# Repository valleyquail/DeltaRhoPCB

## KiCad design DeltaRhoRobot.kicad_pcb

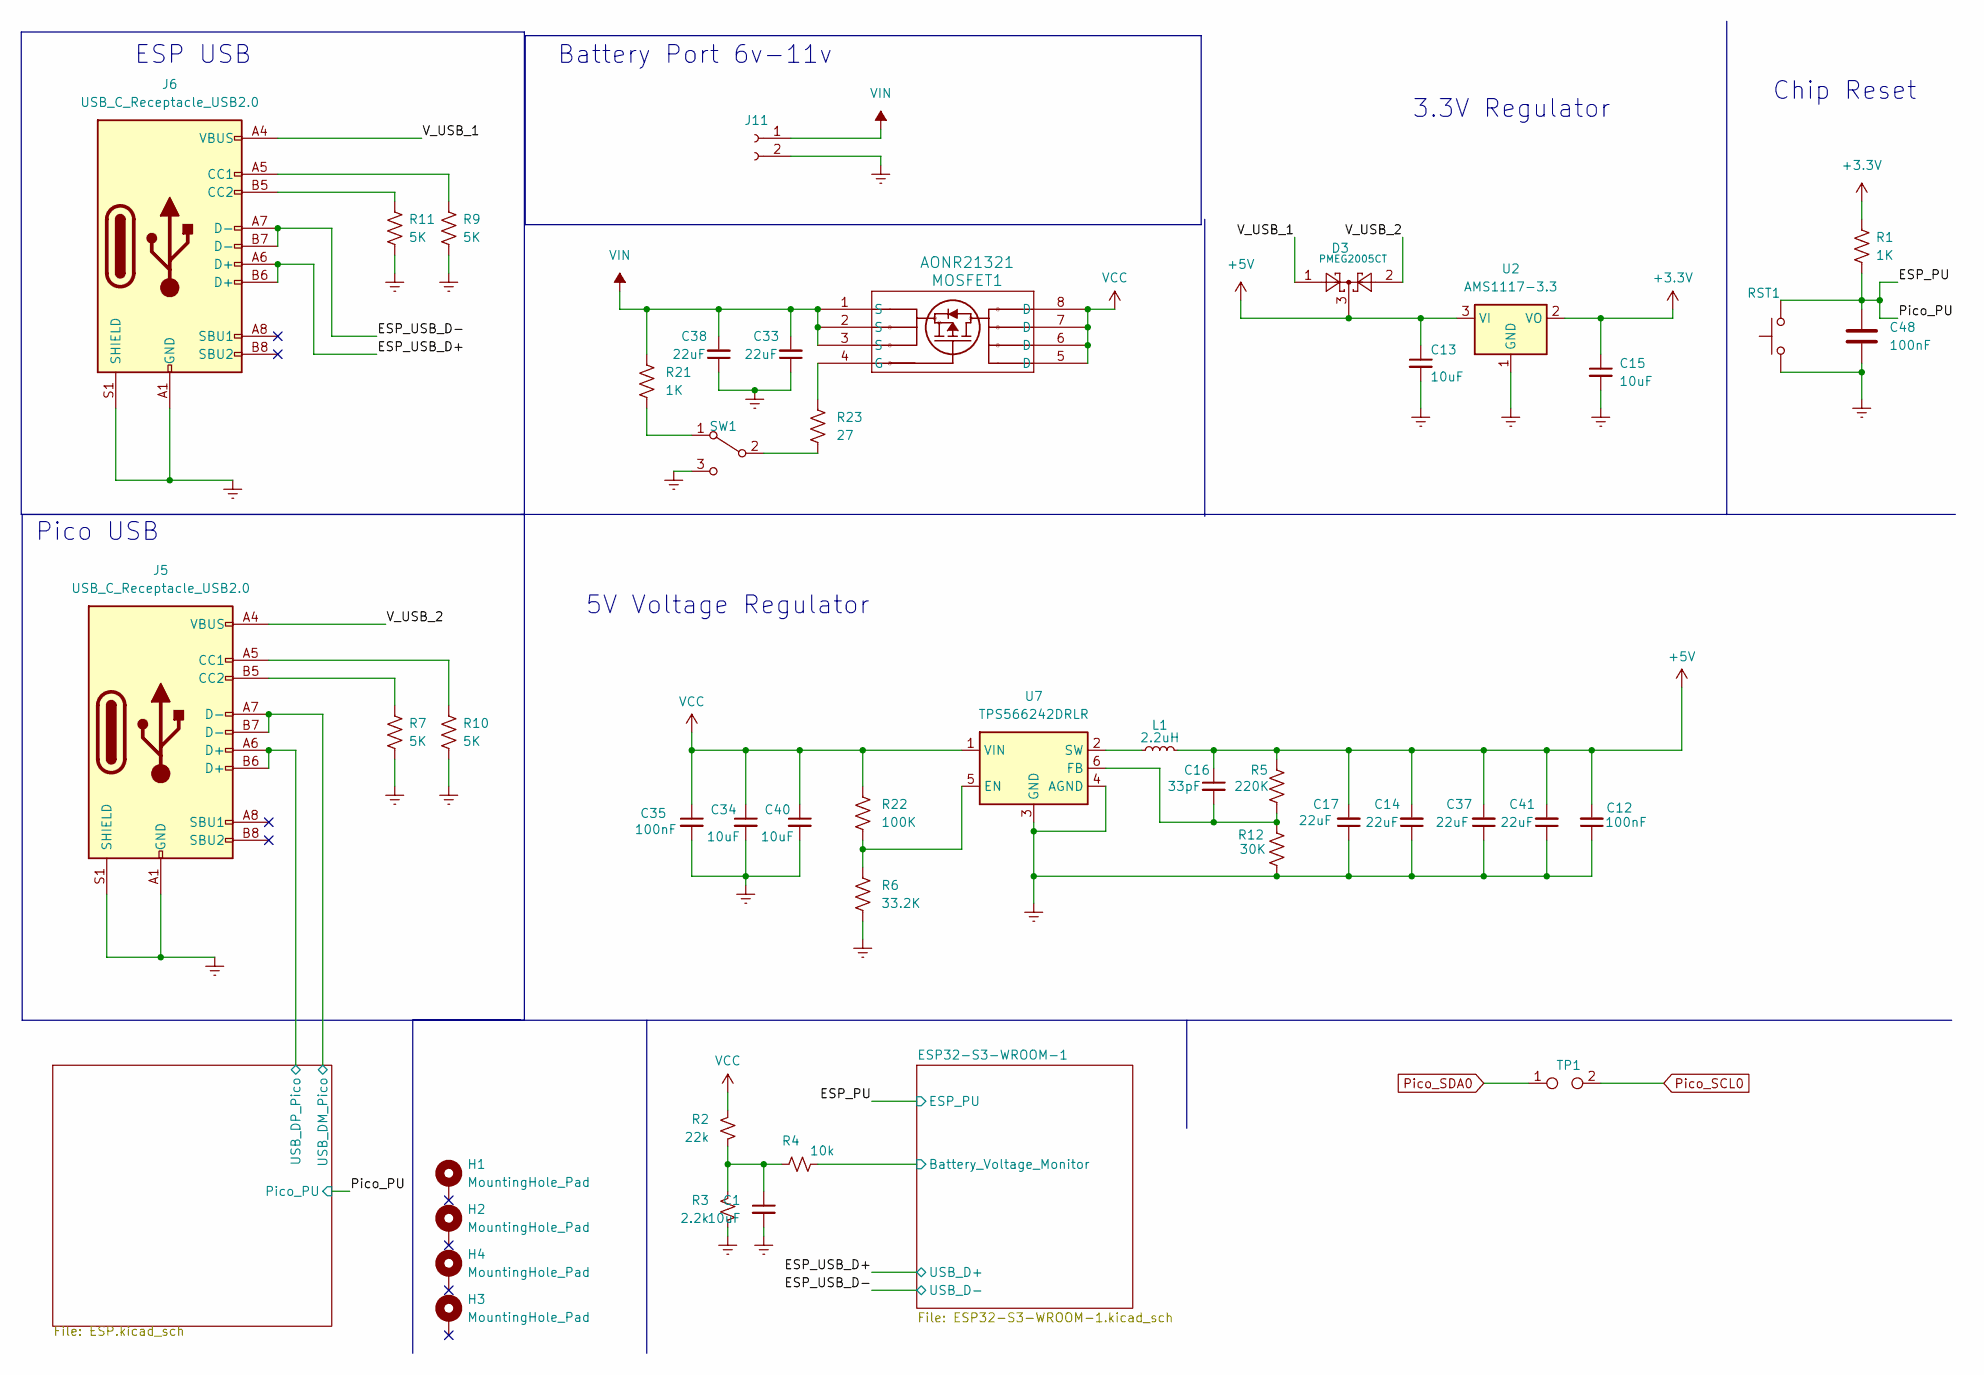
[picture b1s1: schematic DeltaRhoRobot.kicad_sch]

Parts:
C1: 10uF; C_0402_1005Metric; LCSC Part # C15525
C12, C35, C48: 100nF; C_0402_1005Metric; LCSC Part # C307331
C13, C15: 10uF; C_1206_3216Metric; LCSC Part # C13585
C14, C17, C33, C37, C38, C41: 22uF; C_0805_2012Metric; LCSC Part # C45783
C16: 33pF; C_0402_1005Metric; LCSC Part # C1562
C34, C40: 10uF; C_0402_1005Metric; LCSC Part # C1525
D3: PMEG2005CT; SOT-23; LCSC Part # C282562
H1, H2, H3, H4: MountingHole_Pad; MountingHole_3.2mm_M3_ISO14580_Pad_TopOnly
J5, J6: USB_C_Receptacle_USB2.0; USB_C_Receptacle_G-Switch_GT-USB-7010ASV; LCSC Part # C2988369
J11: Conn_01x02_Socket; JST_XH_B2B-XH-A_1x02_P2.50mm_Vertical; LCSC Part # C163035
L1: 2.2uH; HPC 6045NC-2R2M
MOSFET1: AONR21321; DFN8_3x3_EP_AOS; LCSC Part # C541711
R1, R21: 1K; R_0402_1005Metric; LCSC Part # C11702
R2: 22k; R_0402_1005Metric; LCSC Part # C25768
R3: 2.2k; R_0402_1005Metric; LCSC Part # C25879
R4: 10k; R_0402_1005Metric; LCSC Part # C25744
R5: 220K; R_0603_1608Metric
R6: 33.2K; R_0402_1005Metric; LCSC Part # C25779
R7, R9, R10, R11: 5K; R_0402_1005Metric; LCSC Part # C25905
R12: 30K; R_0603_1608Metric; LCSC Part # C22984
R22: 100K; R_0402_1005Metric; LCSC Part # C25741
R23: 27; R_0402_1005Metric; LCSC Part # C25105
RST1: SW_Push; SW_SPST_PTS645; LCSC Part # C221871
SW1: CAS-120A1; 1825232-1_TEC
TP1: TestPoint_2Pole; TestPoint_2Pads_Pitch2.54mm_Drill0.8mm
U2: AMS1117-3.3; SOT-223-3_TabPin2; LCSC Part # C347222
U7: TPS566242DRLR; SOT-563; JLCPCB Rotation Offset -90

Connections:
+3.3V: C15.1, R1.1, U2.2 (VO); also elsewhere on the board
+5V: C12.2, C13.1, C14.2, C16.1, C17.2, C37.2, C41.2, D3.3, L1.2, R5.1, U2.3 (VI); also elsewhere on the board
/ESP32-S3-WROOM-1/Battery_Voltage_Monitor: R4.2; also elsewhere on the board
/ESP_PU: C48.1, R1.2, RST1.1; also elsewhere on the board
/ESP_USB_D+: J6.A6 (D+), J6.B6 (D+); also elsewhere on the board
/ESP_USB_D-: J6.A7 (D-), J6.B7 (D-); also elsewhere on the board
/Pico/USB_DM_Pico: J5.A7 (D-), J5.B7 (D-); also elsewhere on the board
/Pico/USB_DP_Pico: J5.A6 (D+), J5.B6 (D+); also elsewhere on the board
/V_USB_1: D3.1, J6.A4 (VBUS), J6.A9 (VBUS), J6.B4 (VBUS), J6.B9 (VBUS)
/V_USB_2: D3.2, J5.A4 (VBUS), J5.A9 (VBUS), J5.B4 (VBUS), J5.B9 (VBUS)
Earth: C1.2, C12.1, C13.2, C14.1, C15.2, C17.1, C33.1, C34.2, C35.2, C37.1, C38.1, C40.2, C41.1, C48.2, J5.A1 (GND), J5.A12 (GND), J5.B1 (GND), J5.B12 (GND), J5.S1 (SHIELD), J6.A1 (GND), J6.A12 (GND), J6.B1 (GND), J6.B12 (GND), J6.S1 (SHIELD), J11.2, R3.2, R6.2, R7.2, R9.2, R10.2, R11.2, R12.2, RST1.2, SW1.3 (C), U2.1 (GND), U7.3 (GND), U7.4 (AGND); also elsewhere on the board
unnamed: C1.1, R2.2, R3.1, R4.1
unnamed: J5.A5 (CC1), R10.1
unnamed: J5.B5 (CC2), R7.1
unnamed: J6.A5 (CC1), R9.1
unnamed: J6.B5 (CC2), R11.1
unnamed: MOSFET1.4 (G), R23.1
unnamed: R21.2, SW1.1 (A)
unnamed: R23.2, SW1.2 (B)
unnamed: R6.1, R22.2, U7.5 (EN)
unnamed: C16.2, R5.2, R12.1, U7.6 (FB)
unnamed: L1.1, U7.2 (SW)
Pico_SCL0: TP1.2; also elsewhere on the board
Pico_SDA0: TP1.1; also elsewhere on the board
VCC: C34.1, C35.1, C40.1, MOSFET1.5 (D), MOSFET1.6 (D), MOSFET1.7 (D), MOSFET1.8 (D), R2.1, R22.1, U7.1 (VIN); also elsewhere on the board
VIN: C33.2, C38.2, J11.1, MOSFET1.1 (S), MOSFET1.2 (S), MOSFET1.3 (S), R21.1

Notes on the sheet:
5V Voltage Regulator
ESP USB
Chip Reset
Battery Port 6v-11v
Pico USB
3.3V Regulator

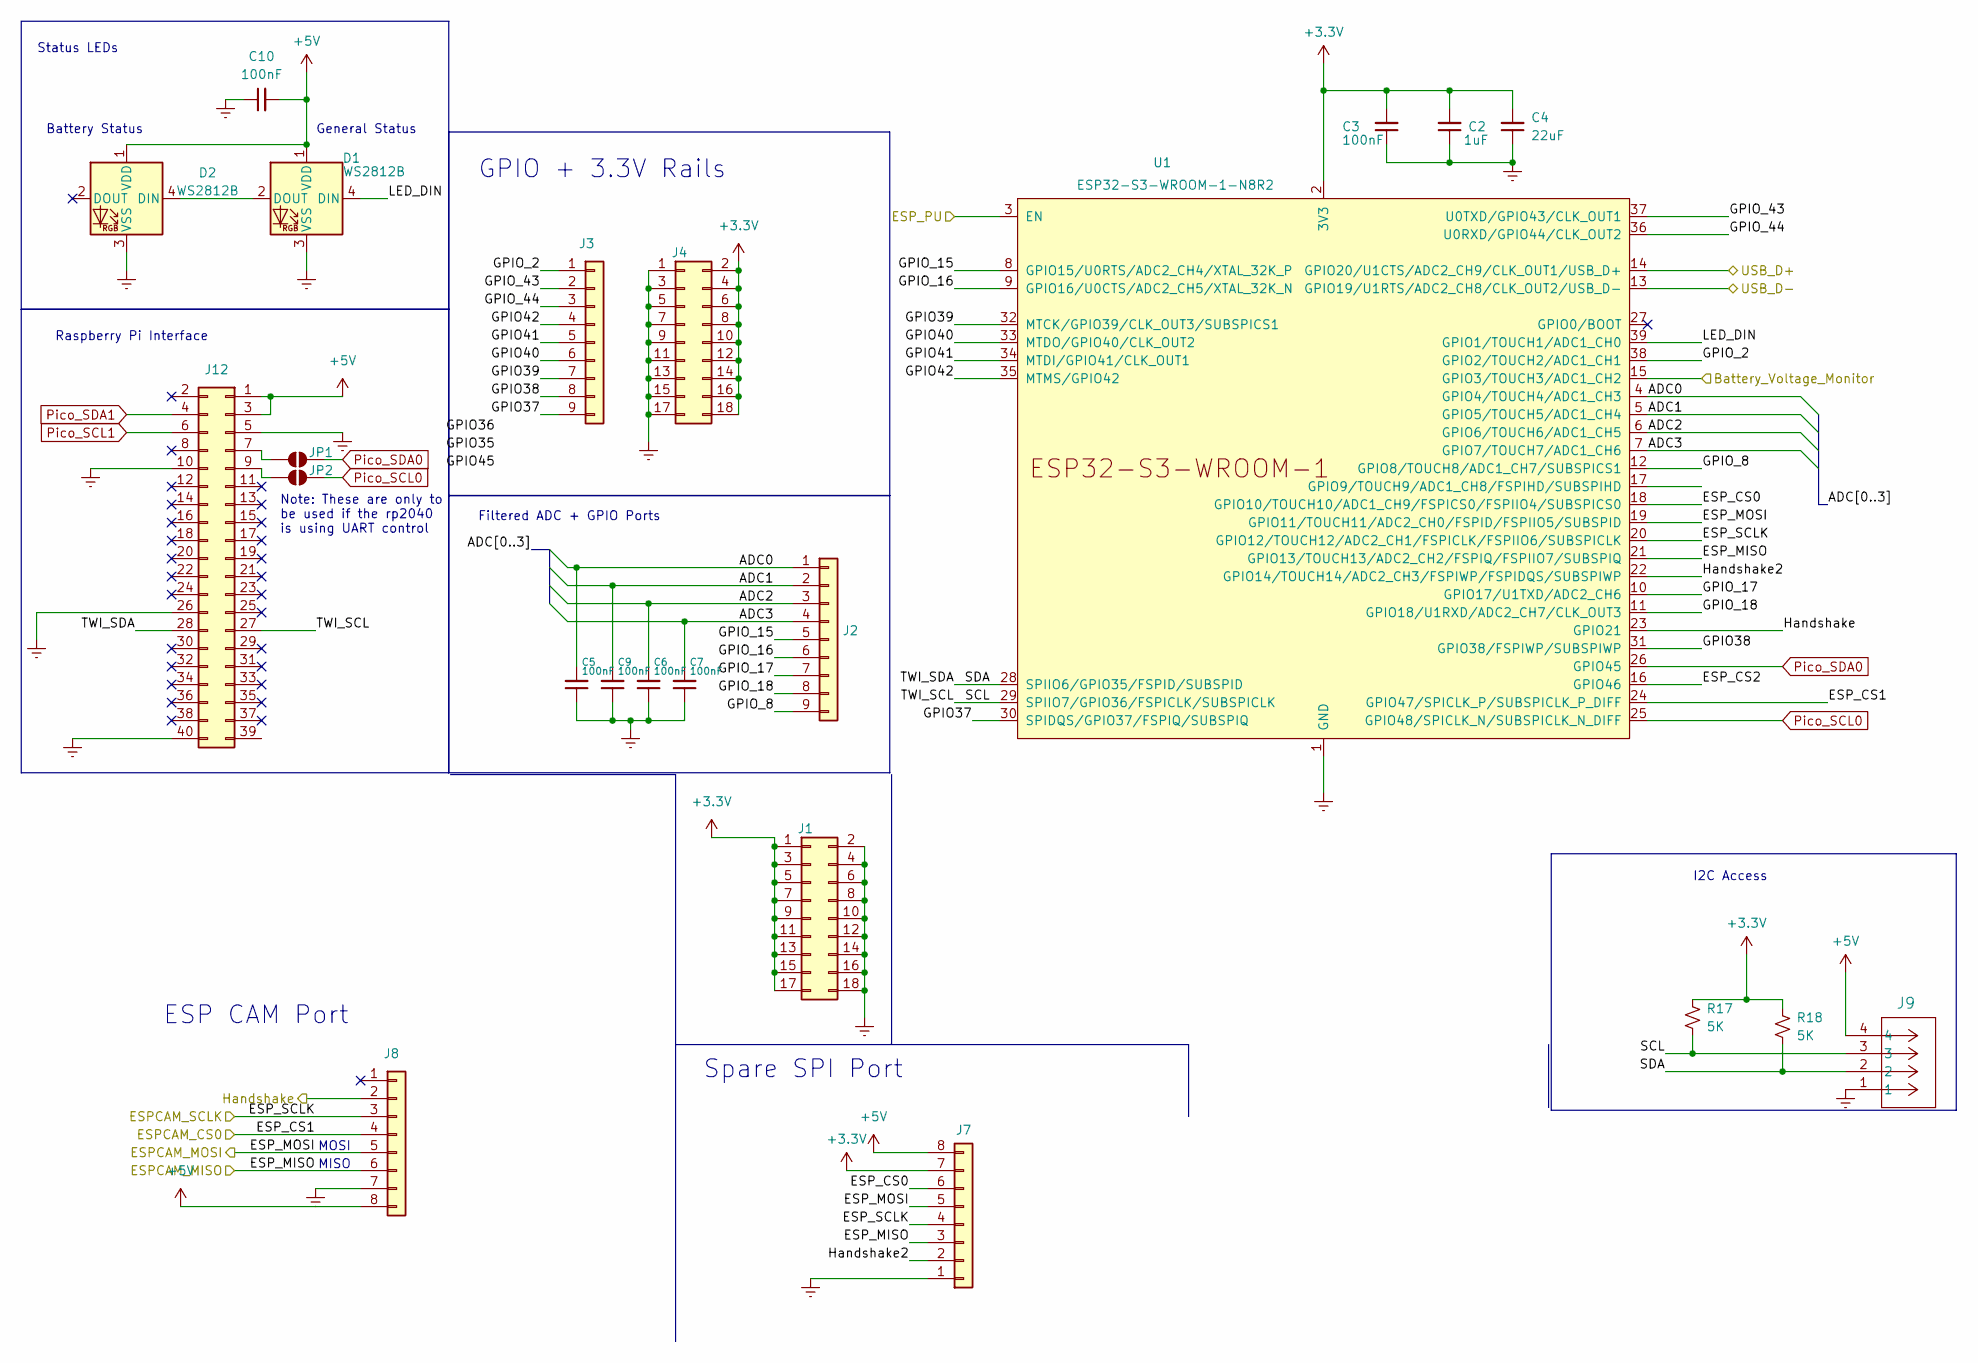
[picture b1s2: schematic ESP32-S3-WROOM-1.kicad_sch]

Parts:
C2: 1uF; C_0402_1005Metric; LCSC Part # C52923
C3, C5, C6, C7, C9, C10: 100nF; C_0402_1005Metric; LCSC Part # C307331
C4: 22uF; C_0603_1608Metric; LCSC Part # C59461
D1, D2: WS2812B; LED_WS2812B_PLCC4_5.0x5.0mm_P3.2mm; LCSC Part # C114586
J1, J4: Conn_02x09_Top_Bottom; PinSocket_2x09_P2.54mm_Vertical
J2, J3: Conn_01x09; PinSocket_1x09_P2.54mm_Vertical
J7, J8: Conn_01x08; PinSocket_1x08_P2.54mm_Vertical
J9: JST-XH; JST_XH_B4B-XH-A_1x04_P2.50mm_Vertical
J12: Conn_02x20_Counter_Clockwise; PinSocket_2x20_P2.54mm_Vertical
JP1, JP2: SolderJumper_2_Open; SolderJumper-2_P1.3mm_Open_RoundedPad1.0x1.5mm
R17, R18: 5K; R_0402_1005Metric; LCSC Part # C25905
U1: ESP32-S3-WROOM-1-N8R2; ESP32-S3-WROOM-1; LCSC Part # C2913204

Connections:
+3.3V: C2.2, C3.2, C4.2, J1.1, J1.3, J1.5, J1.7, J1.9, J1.11, J1.13, J1.15, J1.17, J4.2, J4.4, J4.6, J4.8, J4.10, J4.12, J4.14, J4.16, J4.18, J7.7, R17.1, R18.1, U1.2 (3V3); also elsewhere on the board
+5V: C10.2, D1.1 (VDD), D2.1 (VDD), J7.8, J8.8, J9.4, J12.1, J12.3; also elsewhere on the board
/ESP32-S3-WROOM-1/ADC0: C5.2, J2.1, U1.4 (GPIO4/TOUCH4/ADC1_CH3)
/ESP32-S3-WROOM-1/ADC1: C9.2, J2.2, U1.5 (GPIO5/TOUCH5/ADC1_CH4)
/ESP32-S3-WROOM-1/ADC2: C6.2, J2.3, U1.6 (GPIO6/TOUCH6/ADC1_CH5)
/ESP32-S3-WROOM-1/ADC3: C7.2, J2.4, U1.7 (GPIO7/TOUCH7/ADC1_CH6)
/ESP32-S3-WROOM-1/Battery_Voltage_Monitor: U1.15 (GPIO3/TOUCH3/ADC1_CH2); also elsewhere on the board
/ESP32-S3-WROOM-1/ESP_CS0: J7.6, U1.18 (GPIO10/TOUCH10/ADC1_CH9/FSPICS0/FSPIIO4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)
/ESP32-S3-WROOM-1/ESP_CS1: J8.4, U1.24 (GPIO47/SPICLK_P/SUBSPICLK_P_DIFF)
/ESP32-S3-WROOM-1/ESP_CS2: U1.16 (GPIO46)
/ESP32-S3-WROOM-1/ESP_MISO: J7.3, J8.6, U1.21 (GPIO13/TOUCH13/ADC2_CH2/FSPIQ/FSPIIO7/S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)
/ESP32-S3-WROOM-1/ESP_MOSI: J7.5, J8.5, U1.19 (GPIO11/TOUCH11/ADC2_CH0/FSPID/FSPIIO5/S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)
/ESP32-S3-WROOM-1/ESP_SCLK: J7.4, J8.3, U1.20 (GPIO12/TOUCH12/ADC2_CH1/FSPICLK/FSPIIO6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)
/ESP32-S3-WROOM-1/GPIO37: J3.9, U1.30 (SPIDQS/GPIO37/FSPIQ/SUBSPIQ)
/ESP32-S3-WROOM-1/GPIO38: J3.8, U1.31 (GPIO38/FSPIWP/SUBSPIWP)
/ESP32-S3-WROOM-1/GPIO39: J3.7, U1.32 (MTCK/GPIO39/CLK_OUT3/SUBSPICS1)
/ESP32-S3-WROOM-1/GPIO40: J3.6, U1.33 (MTDO/GPIO40/CLK_OUT2)
/ESP32-S3-WROOM-1/GPIO41: J3.5, U1.34 (MTDI/GPIO41/CLK_OUT1)
/ESP32-S3-WROOM-1/GPIO42: J3.4, U1.35 (MTMS/GPIO42)
/ESP32-S3-WROOM-1/GPIO_2: J3.1, U1.38 (GPIO2/TOUCH2/ADC1_CH1)
/ESP32-S3-WROOM-1/GPIO_8: J2.9, U1.12 (GPIO8/TOUCH8/ADC1_CH7/SUBSPICS1)
/ESP32-S3-WROOM-1/GPIO_15: J2.5, U1.8 (GPIO15/U0RTS/ADC2_CH4/XTAL_32K_P)
/ESP32-S3-WROOM-1/GPIO_16: J2.6, U1.9 (GPIO16/U0CTS/ADC2_CH5/XTAL_32K_N)
/ESP32-S3-WROOM-1/GPIO_17: J2.7, U1.10 (GPIO17/U1TXD/ADC2_CH6)
/ESP32-S3-WROOM-1/GPIO_18: J2.8, U1.11 (GPIO18/U1RXD/ADC2_CH7/CLK_OUT3)
/ESP32-S3-WROOM-1/GPIO_43: J3.2, U1.37 (U0TXD/GPIO43/CLK_OUT1)
/ESP32-S3-WROOM-1/GPIO_44: J3.3, U1.36 (U0RXD/GPIO44/CLK_OUT2)
/ESP32-S3-WROOM-1/Handshake: J8.2, U1.23 (GPIO21)
/ESP32-S3-WROOM-1/Handshake2: J7.2, U1.22 (GPIO14/TOUCH14/ADC2_CH3/FSPIWP/FSPIDQS/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)
/ESP32-S3-WROOM-1/LED_DIN: D1.4 (DIN), U1.39 (GPIO1/TOUCH1/ADC1_CH0)
/ESP32-S3-WROOM-1/SCL: J9.3, J12.27, R17.2, U1.29 (SPIIO7/GPIO36/FSPICLK/SUBSPICLK)
/ESP32-S3-WROOM-1/SDA: J9.2, J12.28, R18.2, U1.28 (SPIIO6/GPIO35/FSPID/SUBSPID)
/ESP_PU: U1.3 (EN); also elsewhere on the board
/ESP_USB_D+: U1.14 (GPIO20/U1CTS/ADC2_CH9/CLK_OUT1/USB_D+); also elsewhere on the board
/ESP_USB_D-: U1.13 (GPIO19/U1RTS/ADC2_CH8/CLK_OUT2/USB_D-); also elsewhere on the board
Earth: C2.1, C3.1, C4.1, C5.1, C6.1, C7.1, C9.1, C10.1, D1.3 (VSS), D2.3 (VSS), J1.2, J1.4, J1.6, J1.8, J1.10, J1.12, J1.14, J1.16, J1.18, J4.1, J4.3, J4.5, J4.7, J4.9, J4.11, J4.13, J4.15, J4.17, J7.1, J8.7, J9.1, J12.5, J12.10, J12.26, J12.40, U1.1 (GND), U1.40 (GND), U1.41 (GND); also elsewhere on the board
unnamed: D1.2 (DOUT), D2.4 (DIN)
unnamed: J12.7, JP1.1 (A)
unnamed: J12.9, JP2.1 (A)
Pico_SCL0: JP2.2 (B), U1.25 (GPIO48/SPICLK_N/SUBSPICLK_N_DIFF); also elsewhere on the board
Pico_SCL1: J12.6; also elsewhere on the board
Pico_SDA0: JP1.2 (B), U1.26 (GPIO45); also elsewhere on the board
Pico_SDA1: J12.4; also elsewhere on the board

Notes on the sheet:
Spare SPI Port
GPIO + 3.3V Rails
ESP CAM Port
Status LEDs
MOSI
General Status
Battery Status
Filtered ADC + GPIO Ports
Note: These are only to be used if the rp2040 is using UART control
Raspberry Pi Interface
MISO
I2C Access

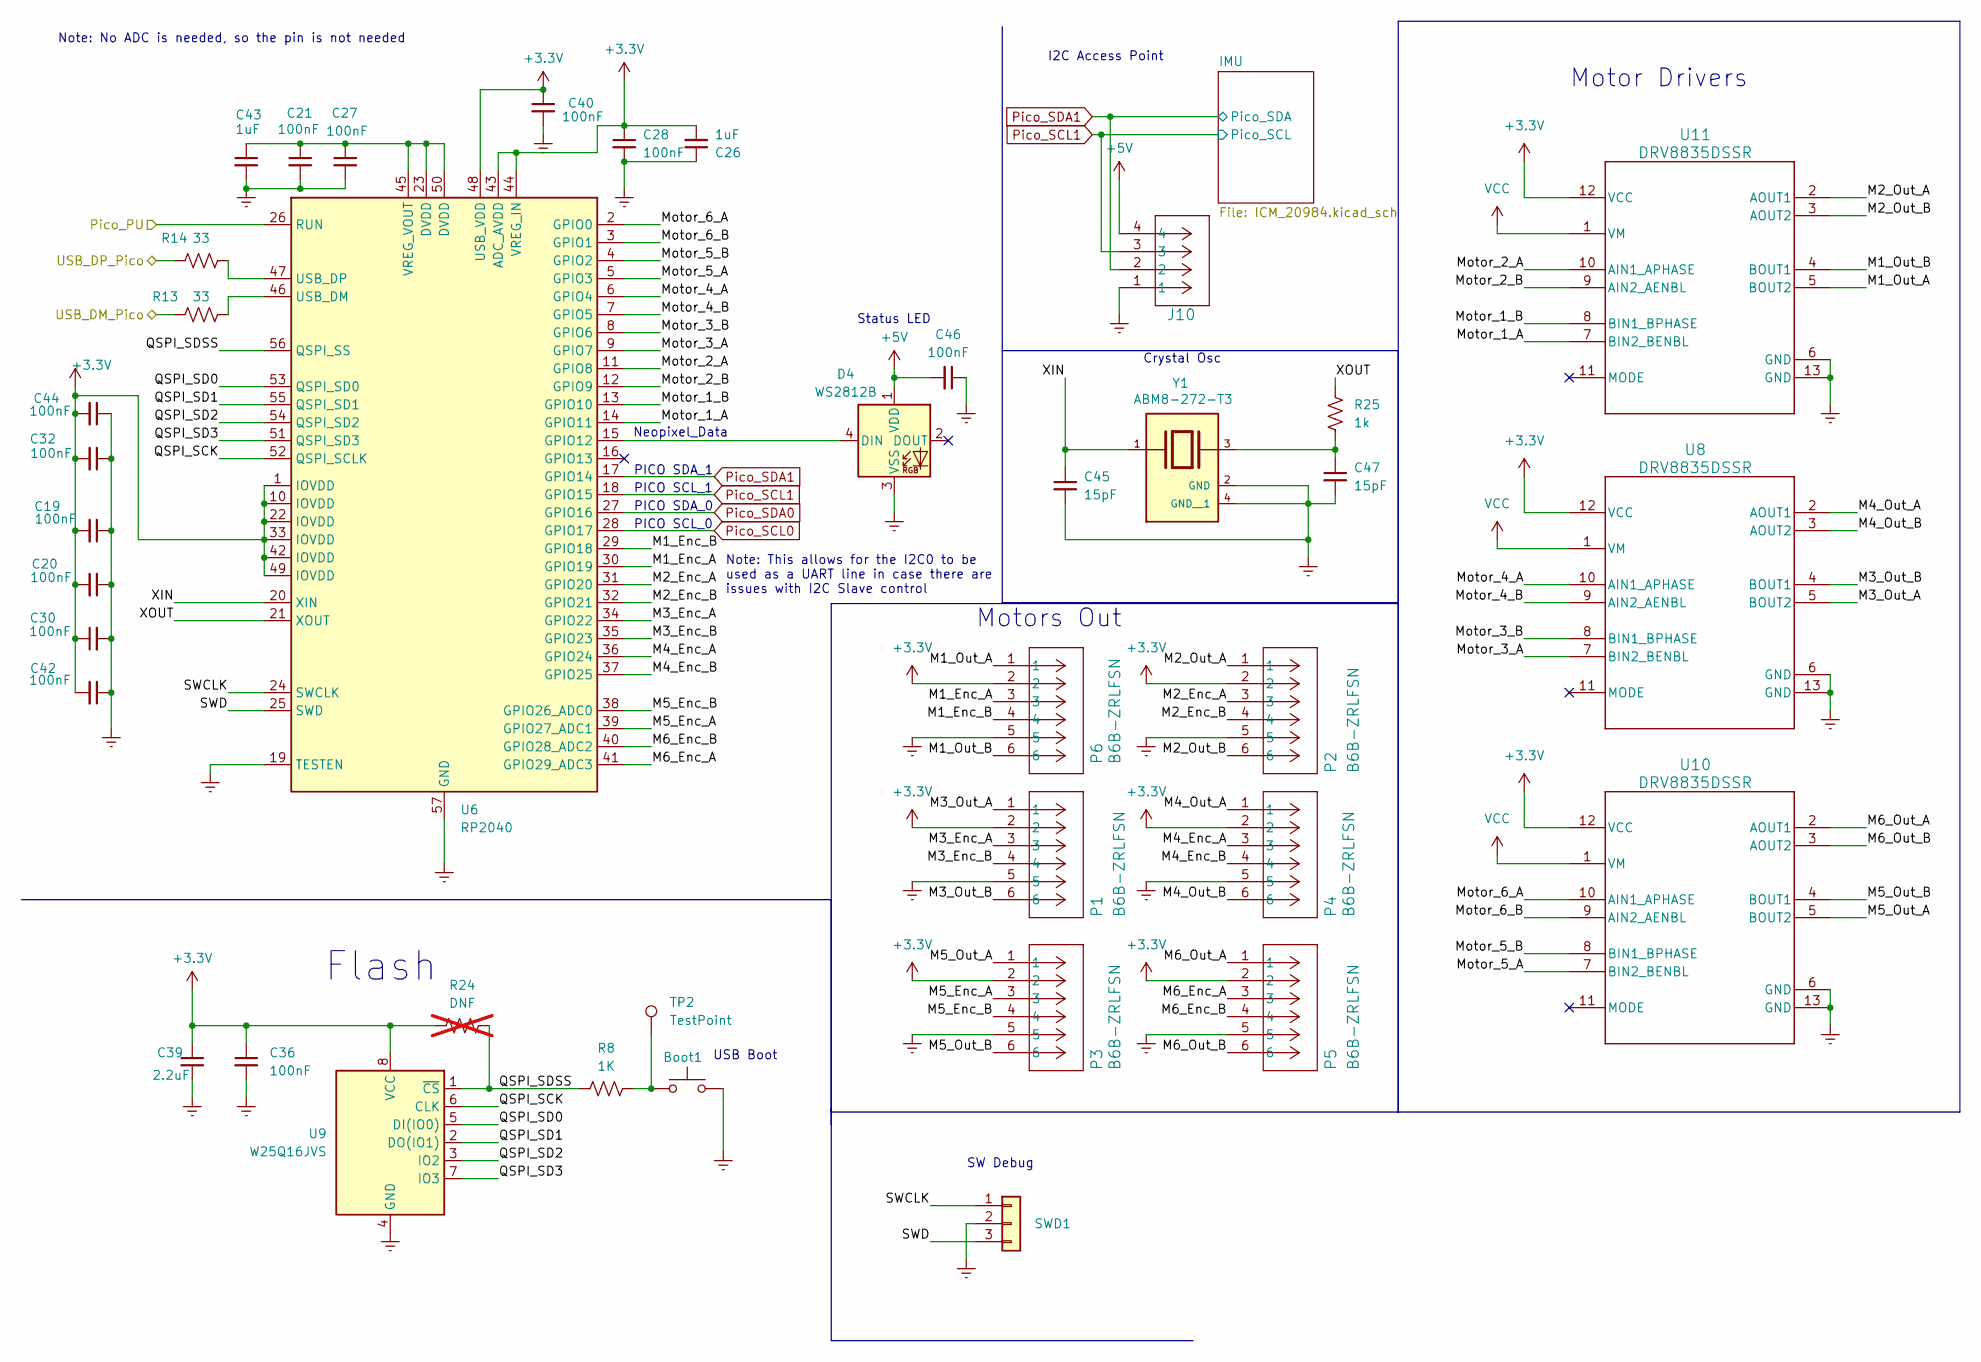
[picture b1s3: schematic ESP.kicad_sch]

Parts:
Boot1: SW_Push; SW_SPST_PTS810; LCSC Part # C116501
C8, C19, C20, C21, C27, C28, C30, C32, C36, C42, C44, C46: 100nF; C_0402_1005Metric; LCSC Part # C307331
C26, C43: 1uF; C_0402_1005Metric; LCSC Part # C52923
C39: 2.2uF; C_0402_1005Metric; LCSC Part # C12530
C45, C47: 15pF; C_0402_1005Metric; LCSC Part # C1548
D4: WS2812B; LED_WS2812B_PLCC4_5.0x5.0mm_P3.2mm; LCSC Part # C114586
J10: JST-XH; JST_XH_B4B-XH-A_1x04_P2.50mm_Vertical
P1, P2, P3, P4, P5, P6: B6B-ZRLFSN; CONN_B6B-ZR_JST
R8: 1K; R_0402_1005Metric; LCSC Part # C11702
R13, R14: 33; R_0402_1005Metric; LCSC Part # C25105
R24: DNF; R_0603_1608Metric_Pad0.98x0.95mm_HandSolder; not fitted
R25: 1k; R_0402_1005Metric; LCSC Part # C11702
SWD1: Conn_01x03; PinHeader_1x03_P2.54mm_Vertical
TP2: TestPoint; TestPoint_Pad_D1.5mm
U6: RP2040; QFN-56-1EP_7x7mm_P0.4mm_EP3.2x3.2mm; LCSC Part # C2040
U8, U10, U11: DRV8835DSSR; WSON-12-1EP_3x2mm_P0.5mm_EP1x2.65_ThermalVias; LCSC Part # C129328
U9: W25Q16JVS; SOIC-8_5.23x5.23mm_P1.27mm
Y1: ABM8-272-T3; Oscillator_SMD_Abracon_ASE-4Pin_3.2x2.5mm; LCSC Part # C5290451

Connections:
+3.3V: C8.1, C19.2, C20.2, C26.2, C28.1, C30.1, C32.2, C36.1, C39.1, C42.2, C44.2, P1.2, P2.2, P3.2, P4.2, P5.2, P6.2, R24.1, U6.1 (IOVDD), U6.10 (IOVDD), U6.22 (IOVDD), U6.33 (IOVDD), U6.42 (IOVDD), U6.43 (ADC_AVDD), U6.44 (VREG_IN), U6.48 (USB_VDD), U6.49 (IOVDD), U8.12 (VCC), U9.8 (VCC), U10.12 (VCC), U11.12 (VCC); also elsewhere on the board
+5V: C46.2, D4.1 (VDD), J10.4; also elsewhere on the board
/ESP_PU: U6.26 (RUN); also elsewhere on the board
/Pico/M1_Enc_A: P6.3, U6.30 (GPIO19)
/Pico/M1_Enc_B: P6.4, U6.29 (GPIO18)
/Pico/M1_Out_A: P6.1, U11.5 (BOUT2)
/Pico/M1_Out_B: P6.6, U11.4 (BOUT1)
/Pico/M2_Enc_A: P2.3, U6.31 (GPIO20)
/Pico/M2_Enc_B: P2.4, U6.32 (GPIO21)
/Pico/M2_Out_A: P2.1, U11.2 (AOUT1)
/Pico/M2_Out_B: P2.6, U11.3 (AOUT2)
/Pico/M3_Enc_A: P1.3, U6.34 (GPIO22)
/Pico/M3_Enc_B: P1.4, U6.35 (GPIO23)
/Pico/M3_Out_A: P1.1, U8.5 (BOUT2)
/Pico/M3_Out_B: P1.6, U8.4 (BOUT1)
/Pico/M4_Enc_A: P4.3, U6.36 (GPIO24)
/Pico/M4_Enc_B: P4.4, U6.37 (GPIO25)
/Pico/M4_Out_A: P4.1, U8.2 (AOUT1)
/Pico/M4_Out_B: P4.6, U8.3 (AOUT2)
/Pico/M5_Enc_A: P3.3, U6.39 (GPIO27_ADC1)
/Pico/M5_Enc_B: P3.4, U6.38 (GPIO26_ADC0)
/Pico/M5_Out_A: P3.1, U10.5 (BOUT2)
/Pico/M5_Out_B: P3.6, U10.4 (BOUT1)
/Pico/M6_Enc_A: P5.3, U6.41 (GPIO29_ADC3)
/Pico/M6_Enc_B: P5.4, U6.40 (GPIO28_ADC2)
/Pico/M6_Out_A: P5.1, U10.2 (AOUT1)
/Pico/M6_Out_B: P5.6, U10.3 (AOUT2)
/Pico/Motor_1_A: U6.14 (GPIO11), U11.7 (BIN2_BENBL)
/Pico/Motor_1_B: U6.13 (GPIO10), U11.8 (BIN1_BPHASE)
/Pico/Motor_2_A: U6.11 (GPIO8), U11.10 (AIN1_APHASE)
/Pico/Motor_2_B: U6.12 (GPIO9), U11.9 (AIN2_AENBL)
/Pico/Motor_3_A: U6.9 (GPIO7), U8.7 (BIN2_BENBL)
/Pico/Motor_3_B: U6.8 (GPIO6), U8.8 (BIN1_BPHASE)
/Pico/Motor_4_A: U6.6 (GPIO4), U8.10 (AIN1_APHASE)
/Pico/Motor_4_B: U6.7 (GPIO5), U8.9 (AIN2_AENBL)
/Pico/Motor_5_A: U6.5 (GPIO3), U10.7 (BIN2_BENBL)
/Pico/Motor_5_B: U6.4 (GPIO2), U10.8 (BIN1_BPHASE)
/Pico/Motor_6_A: U6.2 (GPIO0), U10.10 (AIN1_APHASE)
/Pico/Motor_6_B: U6.3 (GPIO1), U10.9 (AIN2_AENBL)
/Pico/QSPI_SCK: U6.52 (QSPI_SCLK), U9.6 (CLK)
/Pico/QSPI_SD0: U6.53 (QSPI_SD0), U9.5 (DI(IO0))
/Pico/QSPI_SD1: U6.55 (QSPI_SD1), U9.2 (DO(IO1))
/Pico/QSPI_SD2: U6.54 (QSPI_SD2), U9.3 (IO2)
/Pico/QSPI_SD3: U6.51 (QSPI_SD3), U9.7 (IO3)
/Pico/QSPI_SDSS: R8.1, R24.2, U6.56 (QSPI_SS), U9.1 (~CS)
/Pico/SWCLK: SWD1.1, U6.24 (SWCLK)
/Pico/SWD: SWD1.3, U6.25 (SWD)
/Pico/USB_DM_Pico: R13.1; also elsewhere on the board
/Pico/USB_DP_Pico: R14.1; also elsewhere on the board
/Pico/XIN: C45.1, U6.20 (XIN), Y1.1
/Pico/XOUT: R25.1, U6.21 (XOUT)
Earth: Boot1.2, C8.2, C19.1, C20.1, C21.2, C26.1, C27.2, C28.2, C30.2, C32.1, C36.2, C39.2, C42.1, C43.2, C44.1, C45.2, C46.1, C47.2, D4.3 (VSS), J10.1, P1.5, P2.5, P3.5, P4.5, P5.5, P6.5, SWD1.2, U6.19 (TESTEN), U6.57 (GND), U8.6 (GND), U8.13 (GND), U9.4 (GND), U10.6 (GND), U10.13 (GND), U11.6 (GND), U11.13 (GND), Y1.2 (GND), Y1.4 (GND__1); also elsewhere on the board
unnamed: Boot1.1, R8.2, TP2.1
unnamed: C47.1, R25.2, Y1.3
unnamed: D4.4 (DIN), U6.15 (GPIO12)
unnamed: R13.2, U6.46 (USB_DM)
unnamed: R14.2, U6.47 (USB_DP)
unnamed: C21.1, C27.1, C43.1, U6.23 (DVDD), U6.45 (VREG_VOUT), U6.50 (DVDD)
Pico_SCL0: U6.28 (GPIO17); also elsewhere on the board
Pico_SCL1: J10.3, U6.18 (GPIO15); also elsewhere on the board
Pico_SDA0: U6.27 (GPIO16); also elsewhere on the board
Pico_SDA1: J10.2, U6.17 (GPIO14); also elsewhere on the board
VCC: U8.1 (VM), U10.1 (VM), U11.1 (VM); also elsewhere on the board

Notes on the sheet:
PICO SDA_1
PICO SCL_1
Note: This allows for the I2C0 to be used as a UART line in case there are issues with I2C Slave control
Motors Out
Status LED
PICO SCL_0
Neopixel_Data
Flash
Motor Drivers
Note: No ADC is needed, so the pin is not needed
SW Debug
PICO SDA_0
I2C Access Point
Crystal Osc
USB Boot

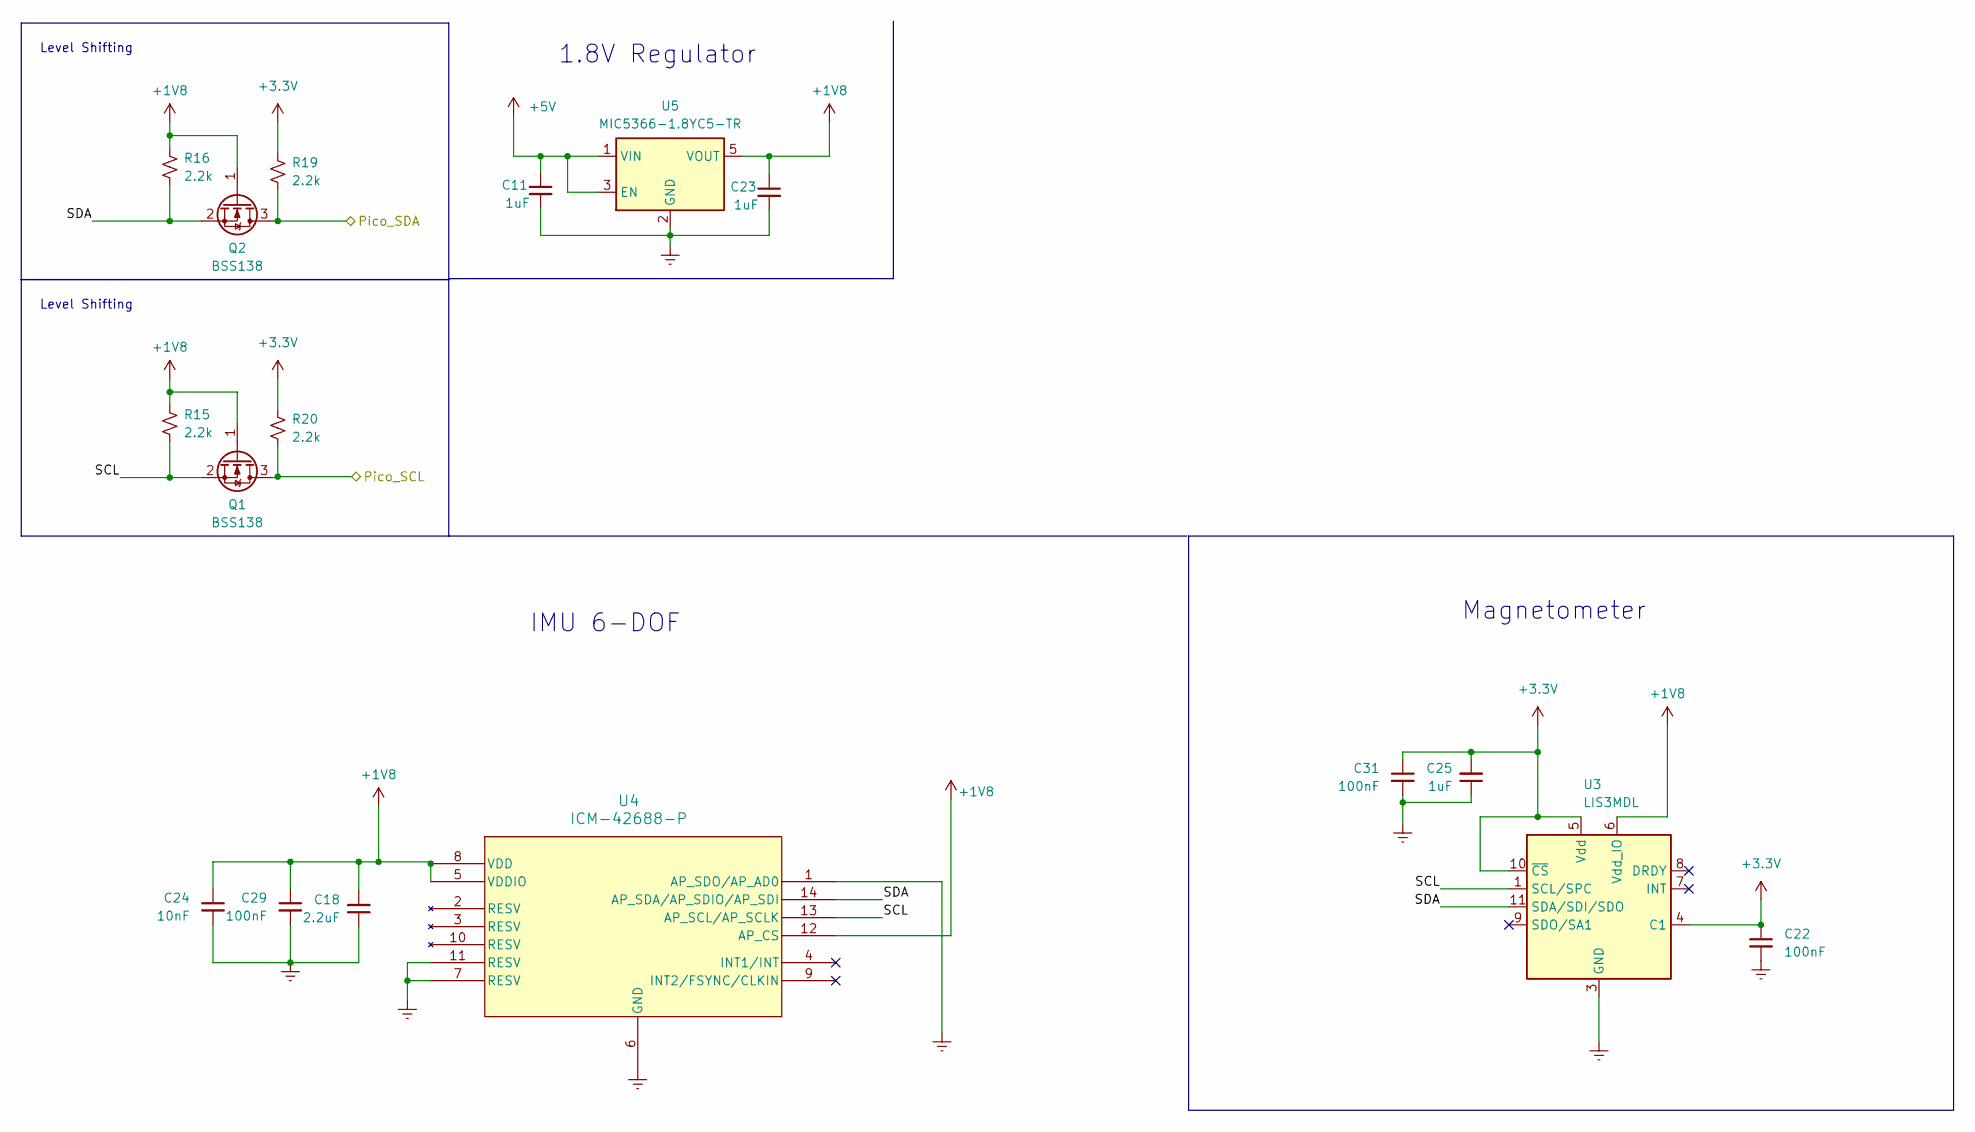
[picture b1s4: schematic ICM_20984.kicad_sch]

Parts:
C11, C23, C25: 1uF; C_0402_1005Metric; LCSC Part # C52923
C18: 2.2uF; C_0402_1005Metric; LCSC Part # C12530
C22, C29, C31: 100nF; C_0402_1005Metric; LCSC Part # C307331
C24: 10nF; C_0402_1005Metric; LCSC Part # C15195
Q1, Q2: BSS138; SOT-23; LCSC Part # C52895
R15, R16, R19, R20: 2.2k; R_0402_1005Metric; LCSC Part # C25879
U3: LIS3MDL; LGA-12_2x2mm_P0.5mm; LCSC Part # C478483
U4: ICM-42688-P; LGA14_2P5X3X0P91_TDK; LCSC Part # C1850418
U5: MIC5366-1.8YC5-TR; SOT-353_SC-70-5; LCSC Part # C3021118

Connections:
+1V8: C18.2, C23.1, C24.1, C29.1, Q1.1 (G), Q2.1 (G), R15.1, R16.1, U3.6 (Vdd_IO), U4.5 (VDDIO), U4.8 (VDD), U4.12 (AP_CS), U5.5 (VOUT)
+3.3V: C22.1, C25.2, C31.1, R19.1, R20.1, U3.4 (C1), U3.5 (Vdd), U3.10 (~CS); also elsewhere on the board
+5V: C11.1, U5.1 (VIN), U5.3 (EN); also elsewhere on the board
/Pico/IMU/SCL: Q1.2 (S), R15.2, U3.1 (SCL/SPC), U4.13 (AP_SCL/AP_SCLK)
/Pico/IMU/SDA: Q2.2 (S), R16.2, U3.11 (SDA/SDI/SDO), U4.14 (AP_SDA/AP_SDIO/AP_SDI)
Earth: C11.2, C18.1, C22.2, C23.2, C24.2, C25.1, C29.2, C31.2, U3.2 (GND), U3.3 (GND), U3.12 (GND), U4.1 (AP_SDO/AP_AD0), U4.6 (GND), U4.7 (RESV), U4.11 (RESV), U5.2 (GND); also elsewhere on the board
Pico_SCL1: Q1.3 (D), R20.2; also elsewhere on the board
Pico_SDA1: Q2.3 (D), R19.2; also elsewhere on the board

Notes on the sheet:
Level Shifting
1.8V Regulator
IMU 6-DOF
Magnetometer

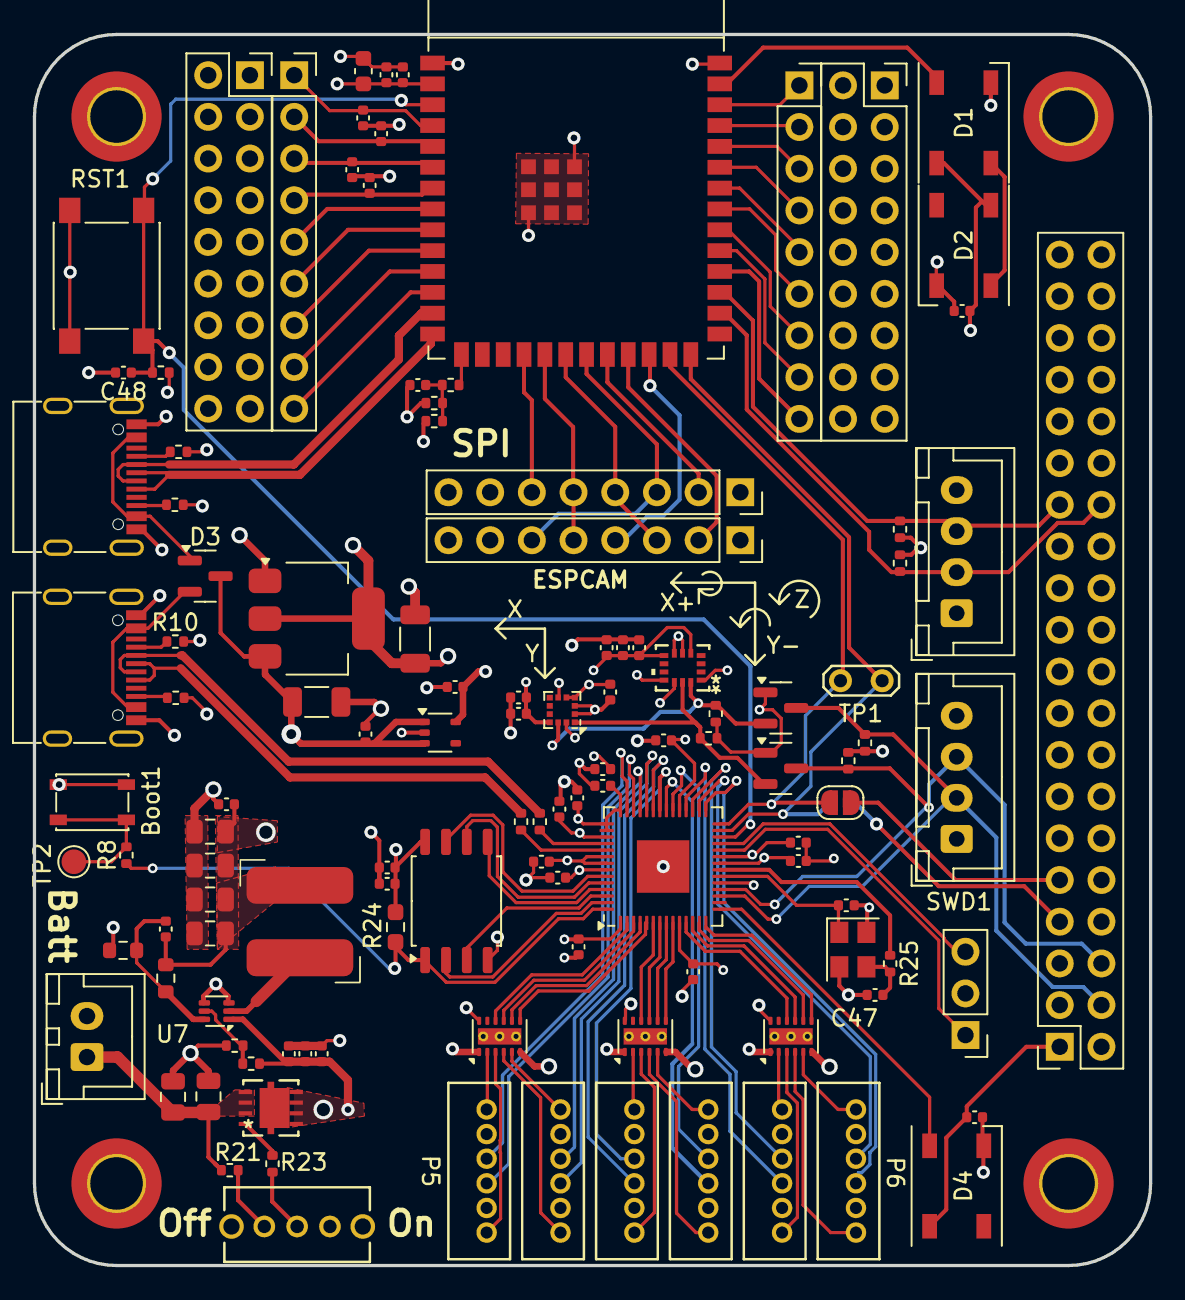
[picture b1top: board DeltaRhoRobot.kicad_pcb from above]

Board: 4 copper layers, 68.0 x 75.0 mm, 122 parts (1 on the bottom side), 114 nets.

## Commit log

2024-01-11 initial
2024-01-12 More progress
2024-01-29 Nearly done schematics
2024-01-31 Much much more progress
2024-02-02 Rev 1
2024-02-02 Cleaning up
2024-02-02 More cleaning
2024-02-02 Clean
2024-02-12 Rev0.1
2024-02-13 clean up Rev
2024-02-14 update to I2C
2024-02-21 Fixed resistors
2024-03-01 V1.0.1
2024-03-21 Removed 201-sized parts
2024-03-22 Replacing ICM-20948
2024-05-21 For production
2024-05-27 JLCniceness
2024-05-30 JLC fixes
2024-06-10 Rev 2 PCB
2024-06-15 Fixing issues
2024-06-18 Rev 2 finished
2024-06-27 Rev 3: fixing I2C and footprints
2024-06-28 Progress
2024-06-28 Layout for 80x80mm done
2024-06-29 Finished new board
2024-06-29 Cleaning
2024-06-29 Silkscreen for orientation
2024-06-29 Small fix
2024-06-29 Graphics and smaller
2024-07-12 Graphics
2024-07-19 Fixed reference errors and bootstrap pin assignments
2024-08-19 Commit message
2024-08-21 Draft power redo
2024-09-10 save
2024-09-25 Adding UART backup
2024-10-28 Final
